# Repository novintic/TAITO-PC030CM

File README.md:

This is a Replica of the TAITO PC0030CM hybrid IC used to manage coin inputs and counters (that red ceramic package thingie). It is used on the Bubble Bobble CPU Board and other TAITO games.

If missing or corrupt, the board will report I/O error.

The coin-counter function has not been tested as we don't have any such counters.

Please understand that we are not able to offer any support. Use at your own risk. Thank you.

NOVINTIC 2026

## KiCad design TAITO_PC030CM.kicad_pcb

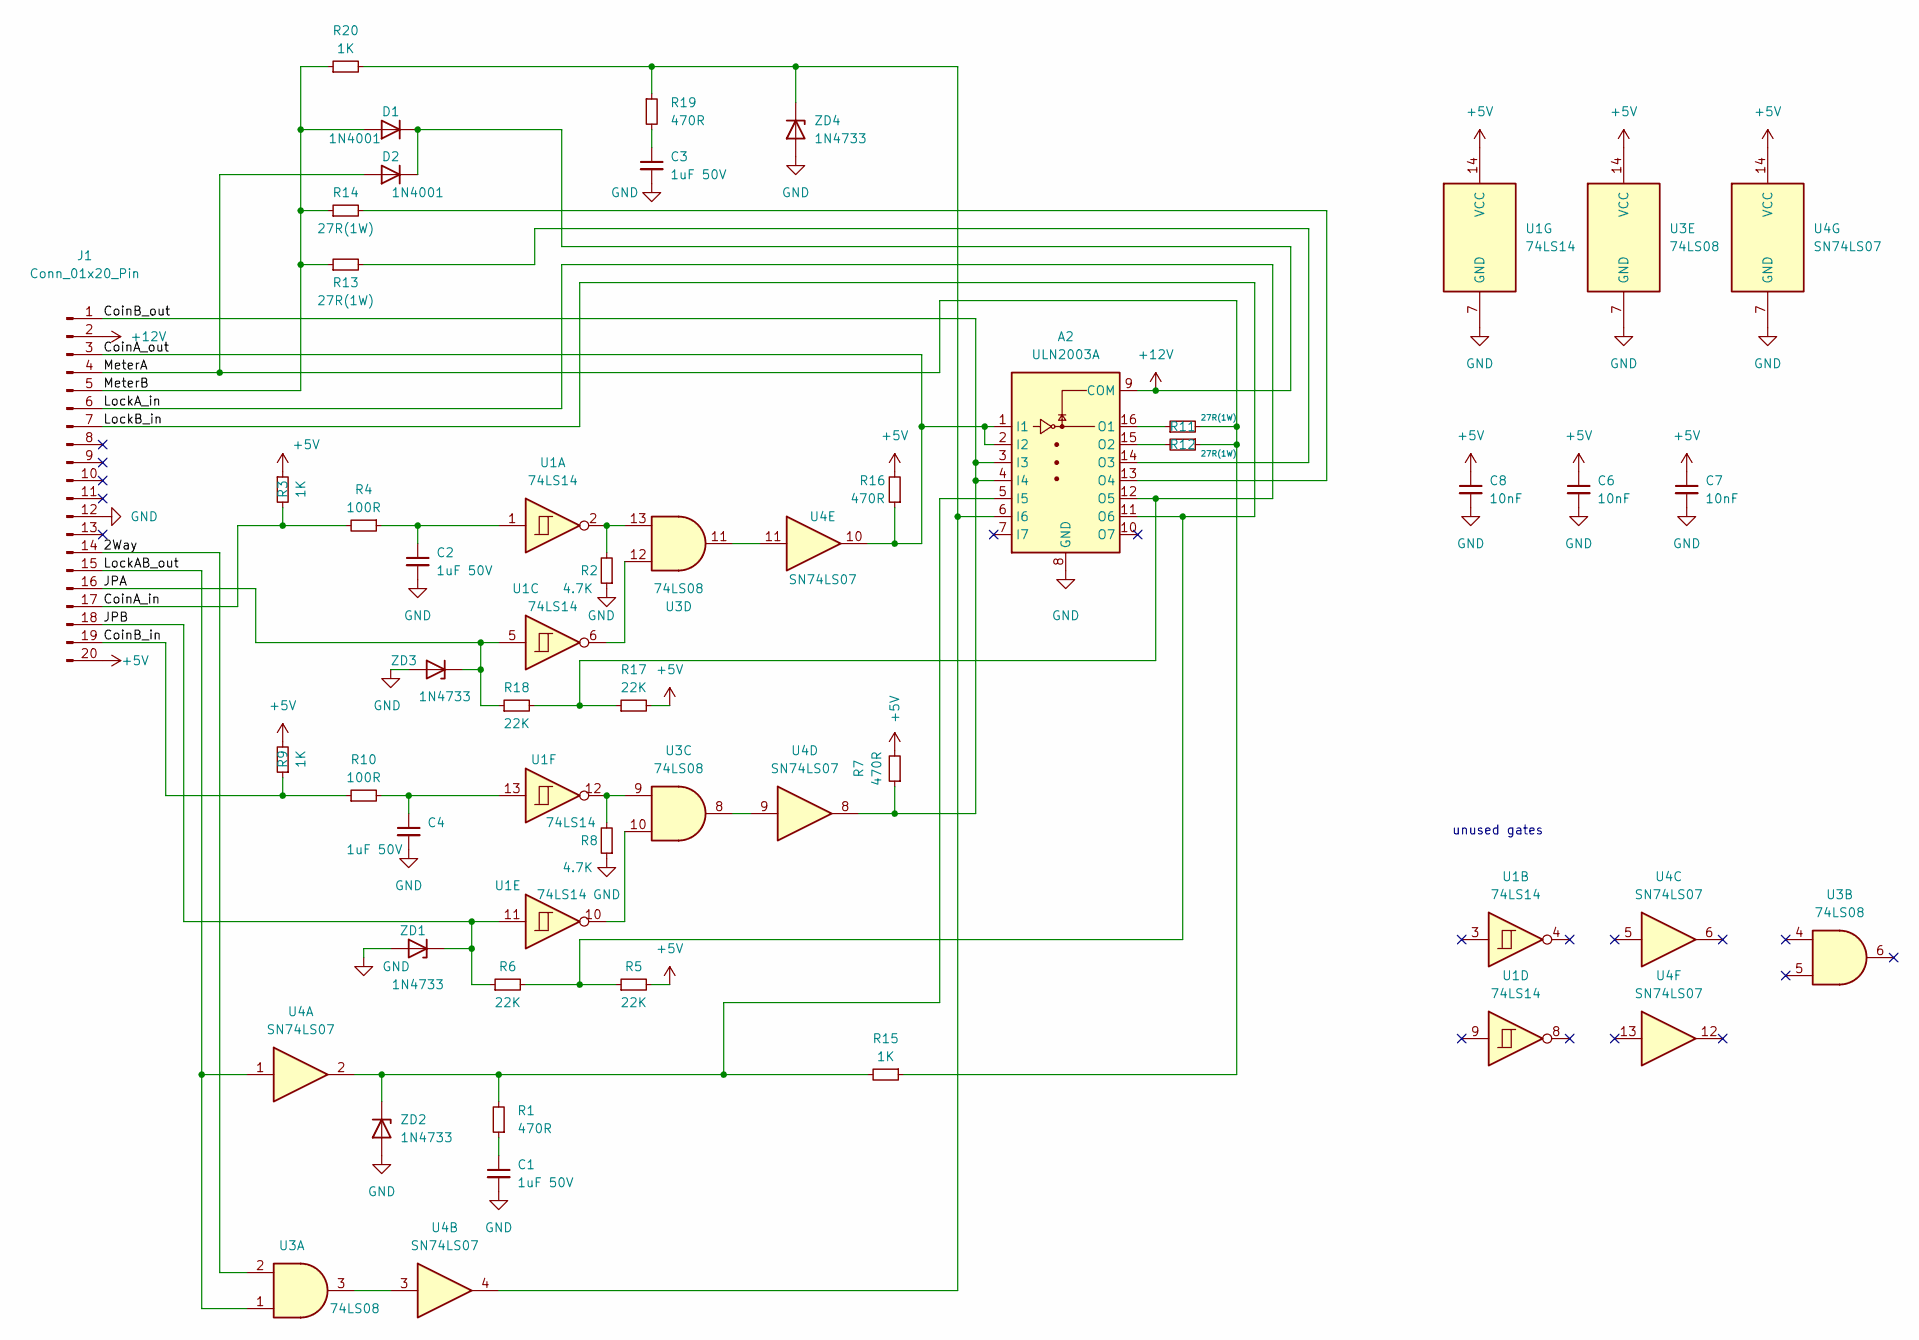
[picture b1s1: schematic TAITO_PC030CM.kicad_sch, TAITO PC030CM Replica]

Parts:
A2: ULN2003A; SOIC-16_3.9x9.9mm_P1.27mm; LCSC C181730
C1, C2, C3, C4: 1uF 50V; C_0805_2012Metric; LCSC C5422
C6, C7, C8: 10nF; C_0805_2012Metric; LCSC C1710
D1, D2: 1N4001; D_SMA; LCSC 1N4001
J1: Conn_01x20_Pin; PinHeader_1x20_P2.54mm_Vertical
R1, R7, R16, R19: 470R; R_0805_2012Metric; LCSC C17710
R2, R8: 4.7K; R_0805_2012Metric; LCSC C17673
R3, R9, R15, R20: 1K; R_0805_2012Metric; LCSC C17513
R4, R10: 100R; R_0805_2012Metric; LCSC C17408
R5, R6, R17, R18: 22K; R_0805_2012Metric; LCSC C101971
R11, R12, R13, R14: 27R(1W); R_2512_6332Metric; LCSC C25478
U1: 74LS14; SOIC-14_3.9x8.7mm_P1.27mm; LCSC C609750
U3: 74LS08; SOIC-14_3.9x8.7mm_P1.27mm; LCSC C521140
U4: SN74LS07; SOIC-14_3.9x8.7mm_P1.27mm; LCSC C513513
ZD1, ZD2, ZD3, ZD4: 1N4733; D_SMA_Handsoldering; LCSC C5266707

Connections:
+5V: C6.1, C7.1, C8.1, J1.20, R3.1, R5.2, R7.2, R9.2, R16.2, R17.2, U1.14 (VCC), U3.14 (VCC), U4.14 (VCC)
+12V: A2.9 (COM), D1.1 (K), D2.1 (K), J1.2
/2Way: J1.14, U3.2
/CoinA_in: J1.17, R3.2, R4.2
/CoinA_out: A2.1 (I1), A2.2 (I2), J1.3, R16.1, U4.10
/CoinB_in: J1.19, R9.1, R10.1
/CoinB_out: A2.3 (I3), A2.4 (I4), J1.1, R7.1, U4.8
/JPA: J1.16, R18.1, U1.5, ZD3.1 (K)
/JPB: J1.18, R6.1, U1.11, ZD1.1 (K)
/LockAB_out: J1.15, U3.1, U4.1
/LockA_in: A2.12 (O5), J1.6, R17.1, R18.2
/LockB_in: A2.11 (O6), J1.7, R5.1, R6.2
/MeterA: D2.2 (A), J1.4, R11.2, R12.1, R15.1
/MeterB: D1.2 (A), J1.5, R13.1, R14.1, R20.1
GND: A2.8 (GND), C1.2, C2.2, C3.2, C4.2, C6.2, C7.2, C8.2, J1.12, R2.1, R8.1, U1.7 (GND), U3.7 (GND), U4.7 (GND), ZD1.2 (A), ZD2.2 (A), ZD3.2 (A), ZD4.2 (A)
unnamed: A2.5 (I5), R1.2, R15.2, U4.2, ZD2.1 (K)
unnamed: A2.6 (I6), R19.1, R20.2, U4.4, ZD4.1 (K)
unnamed: A2.16 (O1), R11.1
unnamed: A2.15 (O2), R12.2
unnamed: A2.14 (O3), R13.2
unnamed: A2.13 (O4), R14.2
unnamed: C1.1, R1.1
unnamed: C2.1, R4.1, U1.1
unnamed: C3.1, R19.2
unnamed: C4.1, R10.2, U1.13
unnamed: R2.2, U1.2, U3.13
unnamed: R8.2, U1.12, U3.9
unnamed: U1.6, U3.12
unnamed: U1.10, U3.10
unnamed: U3.3, U4.3
unnamed: U3.8, U4.9
unnamed: U3.11, U4.11

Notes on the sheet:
unused gates

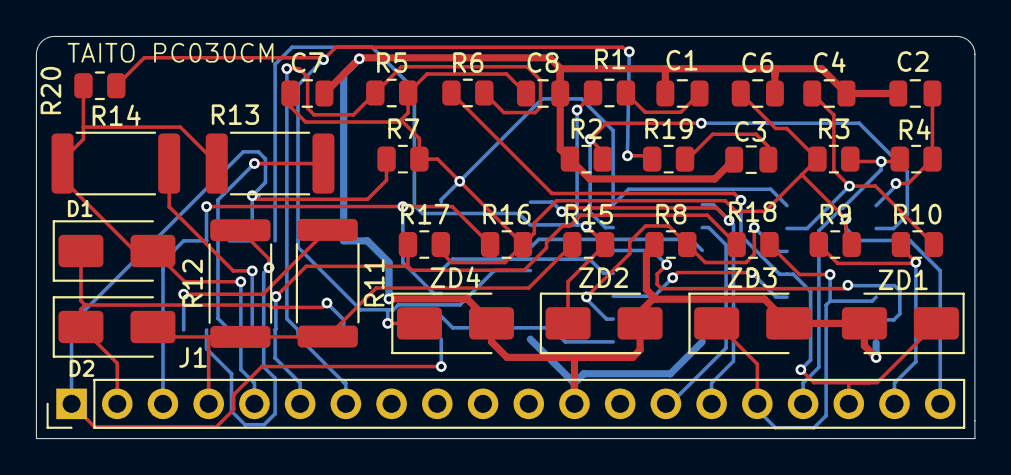
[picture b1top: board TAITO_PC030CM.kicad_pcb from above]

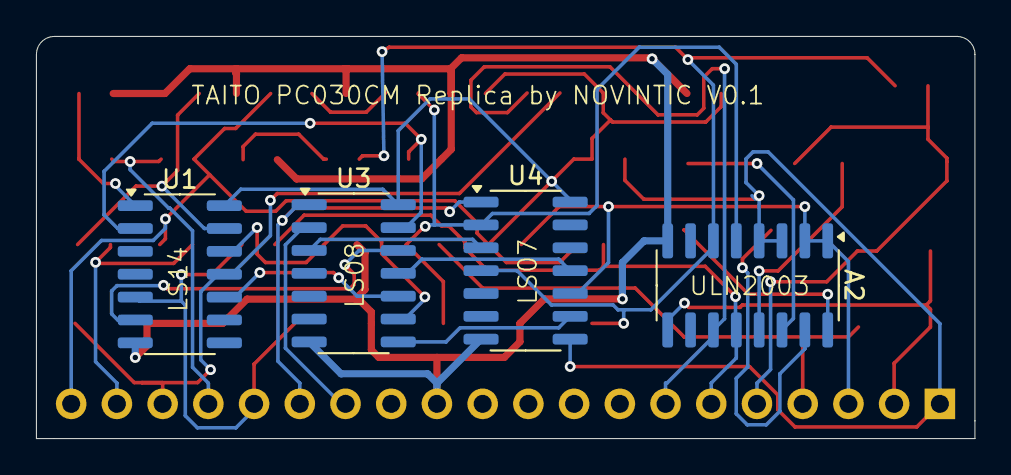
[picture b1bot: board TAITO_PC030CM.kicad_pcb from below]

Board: 2 copper layers, 52.1 x 22.3 mm, 38 parts (4 on the bottom side), 32 nets.
